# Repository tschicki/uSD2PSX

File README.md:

# About This Project

This variant of the [SD2PSX](https://github.com/sd2psx) is made specifically as an accessory for my [PlayStation 2](https://github.com/tschicki/PS2-Portable) portable.  
- Its electronics are based on and essentially 1:1 compatible to the original SD2PSX.  
- Form factor and pinout match an SD card, with one deviation: PS2 memory cards have an ACK signal that SD cards do not have - this is connected to pin 9, instead of DAT2.  
- While the *uSD2PSX* will fit in any SD card slot, only a PS2 will be able to access it.  
- The *uSD2PSX* may be used together with a regular PS2 console too, using a modified Bitfunx MX4SIO memory card.

# Parts Overview
This repo contains the design files (KiCad 7 & SolidWorks Maker) and the manufacturing files for the PCBs and 3D printed parts. Below are the required components to order/print.

## uSD2PSX Base PCB
- [KiCad project](https://github.com/tschicki/uSD2PSX/tree/main/uSD2PSX_Base)
- [Gerber files](https://github.com/tschicki/uSD2PSX/tree/main/uSD2PSX_Base/Gerber)
- [BOM](https://github.com/tschicki/uSD2PSX/tree/main/uSD2PSX_Base/bom)
- Supplier: JLCPCB
- Type: 2-Layer rigid
- Thickness: 0.6mm
- Copper: 1oz
- Plating: ENIG
- Via: tented or plugged

## uSD2PSX Contacts PCB
- [KiCad project](https://github.com/tschicki/uSD2PSX/tree/main/uSD2PSX_Contacts)
- [Gerber files](https://github.com/tschicki/uSD2PSX/tree/main/uSD2PSX_Contacts/Gerber)
- BOM: N/A
- Supplier: JLCPCB
- Type: 2-Layer rigid
- Thickness: 0.8mm
- Copper: 1oz
- Plating: ENIG
- Via: tented or plugged

## uSD2PSX Needle Probe
- [KiCad project](https://github.com/tschicki/uSD2PSX/tree/main/uSD2PSX_Adapter)
- [Gerber files](https://github.com/tschicki/uSD2PSX/tree/main/uSD2PSX_Adapter/Gerber)
- [BOM](https://github.com/tschicki/uSD2PSX/tree/main/uSD2PSX_Adapter/bom)
- Supplier: JLCPCB
- Type: 2-Layer rigid
- Thickness: 1.2mm
- Copper: 1oz
- Plating: HASL
- Via: tented or plugged

## uSD2PSX Cover
- [STEP & STL](https://github.com/tschicki/uSD2PSX/tree/main/uSD2PSX_3D/Export)
- 3D printed at 0.12mm layer height

## uSD2PSX Needle Probe Parts
- *Clip* and *Aligner*
- [STEP & STL](https://github.com/tschicki/uSD2PSX/tree/main/uSD2PSX_3D/Export)
- 3D printed

# Assembly uSD2PSX

## CBA Assembly
- First populate the *uSD2PSX Base* PCB according to its BOM, either manually or with stencil & paste. 
- Apply solder/paste on the pads intended for the *uSD2PSX Contacts* PCB and place it there. 
- Heat the assembly either with hot air or in a reflow oven and ensure that Base & Contacts are aligned without a gap between them.
- Check for shorts and clean the resulting assembly.

## SD Card Preparation
- Download the latest the SD2PSXtd firmware for SD2PSX. Find it [here](https://sd2psxtd.github.io).
- [PS2 Homebre Store](https://ps2homebrewstore.com/exploits/loadbooter-sd2psx/) has an awesome SD2PSX setup guide and pre-configured SD card image
- Prepare the SD card according to the instructions there

## Programming
- Plug the prepared micro SD card into the *uSD2PSX* assembly
- Place the assembly in the *uSD2PSX* Needle Probe and close it.
- Enter the RP2040 USB bootloader by plugging the *uSD2PSX Needle Probe* into a PC while holding the Bootsel button
- Drag the SD2PSXtd firmware image (.uf2) into the SD2PSX explorer window
- Unplug the *uSD2PSX Needle Probe*

## Setup
- Plug the *uSD2PSX Needle Probe* back into the PC
- The OLED should now display the SD2PSX menu, use the buttons SW1 and SW2 to navigate it
- Deploy CIV.bin in the menu
- Set Autoboot=ON and Mode=PS2 in the menu
- The *uSD2PSX* should now be configured, unplug it and preferrably give it a try on a PS2
- When you are sure that the *uSD2PSX* works as intended, adhere the *uSD2PSX Cover* using 2-3 small drops of glue. Ensure that no glue enters the micro SD card slot.
- As a last step, add a sticker on the top side to protect the testpoints, it should be betwen 0.1 and 0.2mm thickness

# Assembly uSD2PSX Needle Probe

- Populate the *uSD2PSX Needle Probe* CBA according to its BOM
- Clean the assembly
- Solder the 0.96 inch I2C OLED (same as SD2PSX) to the CBA
- Fix the printed Aligner to the CBA using 4 M1.6x5mm screws

# Modify a MX4SIO to work with uSD2PSX

The easiest and cleanest looking way to connect the *uSD2PSX* to a stock console is to modify a Bitfunx MX4SIO adapter.  
Buy a Bitfunx MX4SIO with SD card slot (beware, they also sell micro SD versions!) and open it up.
Remove R5 and solder a wire from it to the leftmost pin of the SD card slot. This will connect the ACK signal back to its original pin.

# Thanks!
Thanks to everyone working on SD2PSX and the awesome SD2PSXtd firmware!  
And thanks to everyone involved in [PS2 Homebre Store](https://ps2homebrewstore.com), it's awesome to see easily accessible apps and guides!

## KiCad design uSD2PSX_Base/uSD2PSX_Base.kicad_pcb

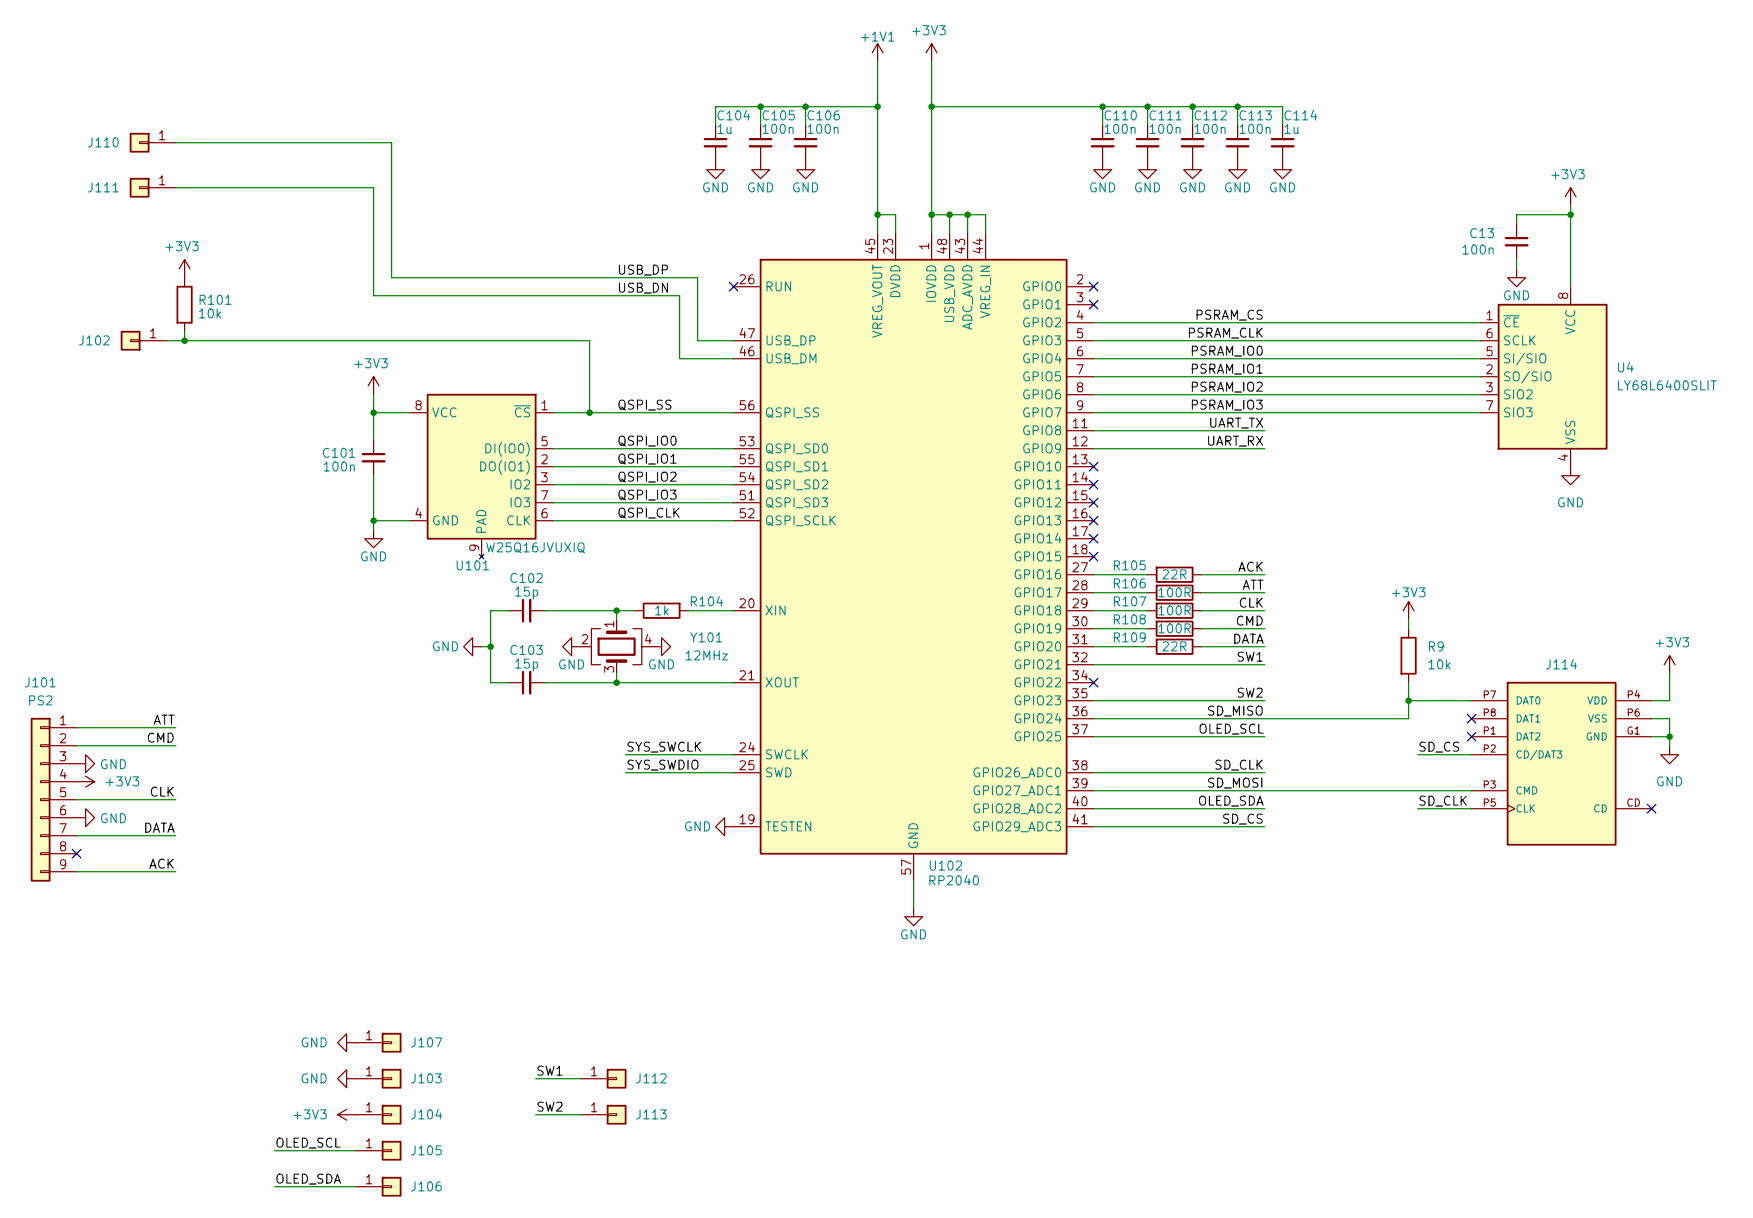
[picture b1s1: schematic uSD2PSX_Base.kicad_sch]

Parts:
C13, C101, C105, C106, C110, C111, C112, C113: 100n; C_0402_1005Metric; Part Number CC0402KRX7R7BB104
C102, C103: 15p; C_0402_1005Metric; Part Number CC0402JRNPO9BN150
C104, C114: 1u; C_0402_1005Metric; Part Number CC0603KRX7R7BB105
J101: PS2; uSD2PSX_Base
J102: BSEL; TestPoint_Pad_D1.5mm
J103, J107, J112: GND; TestPoint_Pad_D1.5mm
J104, J113: 3V3; TestPoint_Pad_D1.5mm
J105: SCL; TestPoint_Pad_D1.5mm
J106: SDA; TestPoint_Pad_D1.5mm
J110: DP; TestPoint_Pad_D1.5mm
J111: DN; TestPoint_Pad_D1.5mm
J114: MEM2085-00-115-00-A_REV0.2; GCT_MEM2085-00-115-00-A_REV0.2; Part Number MEM2085-00-115-00-A
R9, R101: 10k; R_0402_1005Metric; Part Number RC0402JR-0710KL
R104: 1k; R_0402_1005Metric; Part Number RC0402FR-071KL
R105, R109: 22R; R_0402_1005Metric; Part Number RC0402FR-0722RL
R106, R107, R108: 100R; R_0402_1005Metric; Part Number RC0402JR-07100RL
U4: LY68L6400SLIT; IC_W25Q16JVUXIQ_TR; Part Number APS6404L-3SQR-ZR; LCSC C261881
U101: W25Q16JVUXIQ; WSON-8-1EP_6x5mm_P1.27mm_EP3.4x4.3mm; Part Number W25Q16JVUXIQ TR
U102: RP2040; QFN-56-1EP_7x7mm_P0.4mm_EP3.2x3.2mm; Part Number RP2040
Y101: 12MHz; Crystal_SMD_3225-4Pin_3.2x2.5mm; Part Number FL1200112

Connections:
+1V1: C104.1, C105.1, C106.1, U102.23 (DVDD), U102.45 (VREG_VOUT), U102.50 (DVDD)
+3V3: C13.1, C101.1, C110.1, C111.1, C112.1, C113.1, C114.1, J101.4, J104.1, J114.P4 (VDD), R9.1, R101.1, U4.8 (VCC), U101.8 (VCC), U102.1 (IOVDD), U102.10 (IOVDD), U102.22 (IOVDD), U102.33 (IOVDD), U102.42 (IOVDD), U102.43 (ADC_AVDD), U102.44 (VREG_IN), U102.48 (USB_VDD), U102.49 (IOVDD)
/ACK: J101.9, R105.1
/ATT: J101.1, R106.1
/CLK: J101.5, R107.1
/CMD: J101.2, R108.1
/DATA: J101.7, R109.1
/OLED_SCL: J105.1, U102.37 (GPIO25)
/OLED_SDA: J106.1, U102.40 (GPIO28_ADC2)
/PSRAM_CLK: U4.6 (SCLK), U102.5 (GPIO3)
/PSRAM_CS: U4.1 (~CE), U102.4 (GPIO2)
/PSRAM_IO0: U4.5 (SI/SIO), U102.6 (GPIO4)
/PSRAM_IO1: U4.2 (SO/SIO), U102.7 (GPIO5)
/PSRAM_IO2: U4.3 (SIO2), U102.8 (GPIO6)
/PSRAM_IO3: U4.7 (SIO3), U102.9 (GPIO7)
/QSPI_CLK: U101.6 (CLK), U102.52 (QSPI_SCLK)
/QSPI_IO0: U101.5 (DI(IO0)), U102.53 (QSPI_SD0)
/QSPI_IO1: U101.2 (DO(IO1)), U102.55 (QSPI_SD1)
/QSPI_IO2: U101.3 (IO2), U102.54 (QSPI_SD2)
/QSPI_IO3: U101.7 (IO3), U102.51 (QSPI_SD3)
/QSPI_SS: J102.1, R101.2, U101.1 (~CS), U102.56 (QSPI_SS)
/SD_CLK: J114.P5 (CLK), U102.38 (GPIO26_ADC0)
/SD_CS: J114.P2 (CD/DAT3), U102.41 (GPIO29_ADC3)
/SD_MISO: J114.P7 (DAT0), R9.2, U102.36 (GPIO24)
/SD_MOSI: J114.P3 (CMD), U102.39 (GPIO27_ADC1)
/SW1: J112.1, U102.32 (GPIO21)
/SW2: J113.1, U102.35 (GPIO23)
/SYS_SWCLK: U102.24 (SWCLK)
/SYS_SWDIO: U102.25 (SWD)
/UART_RX: U102.12 (GPIO9)
/UART_TX: U102.11 (GPIO8)
/USB_DN: J111.1, U102.46 (USB_DM)
/USB_DP: J110.1, U102.47 (USB_DP)
GND: C13.2, C101.2, C102.1, C103.1, C104.2, C105.2, C106.2, C110.2, C111.2, C112.2, C113.2, C114.2, J101.3, J101.6, J103.1, J107.1, J114.G1 (GND), J114.G2 (GND__1), J114.G3 (GND__2), J114.G4 (GND__3), J114.G5 (GND__4), J114.G6 (GND__5), J114.G7 (GND__6), J114.G8 (GND__7), J114.G9 (GND__8), J114.G10 (GND__9), J114.P6 (VSS), U4.4 (VSS), U101.4 (GND), U102.19 (TESTEN), U102.57 (GND), Y101.2, Y101.4
unnamed: C102.2, R104.1, Y101.1
unnamed: R105.2, U102.27 (GPIO16)
unnamed: R106.2, U102.28 (GPIO17)
unnamed: R107.2, U102.29 (GPIO18)
unnamed: R108.2, U102.30 (GPIO19)
unnamed: R109.2, U102.31 (GPIO20)
unnamed: R104.2, U102.20 (XIN)
unnamed: C103.2, U102.21 (XOUT), Y101.3

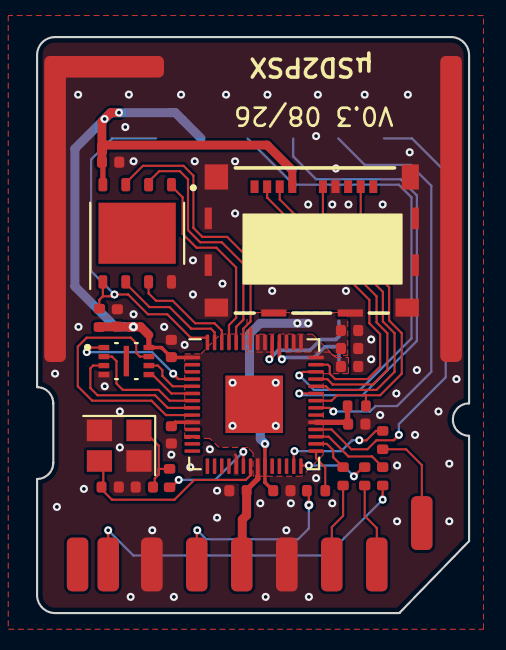
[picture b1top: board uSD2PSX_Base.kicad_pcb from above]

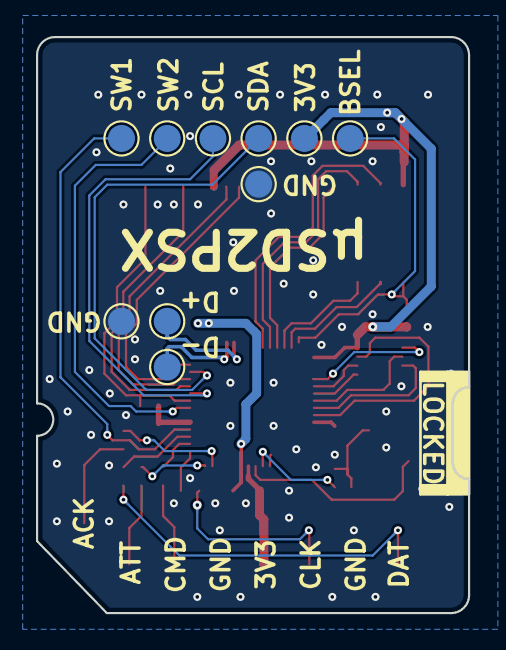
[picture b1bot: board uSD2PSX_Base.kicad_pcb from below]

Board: 2 copper layers, 24.0 x 32.0 mm, 36 parts (11 on the bottom side), 38 nets.

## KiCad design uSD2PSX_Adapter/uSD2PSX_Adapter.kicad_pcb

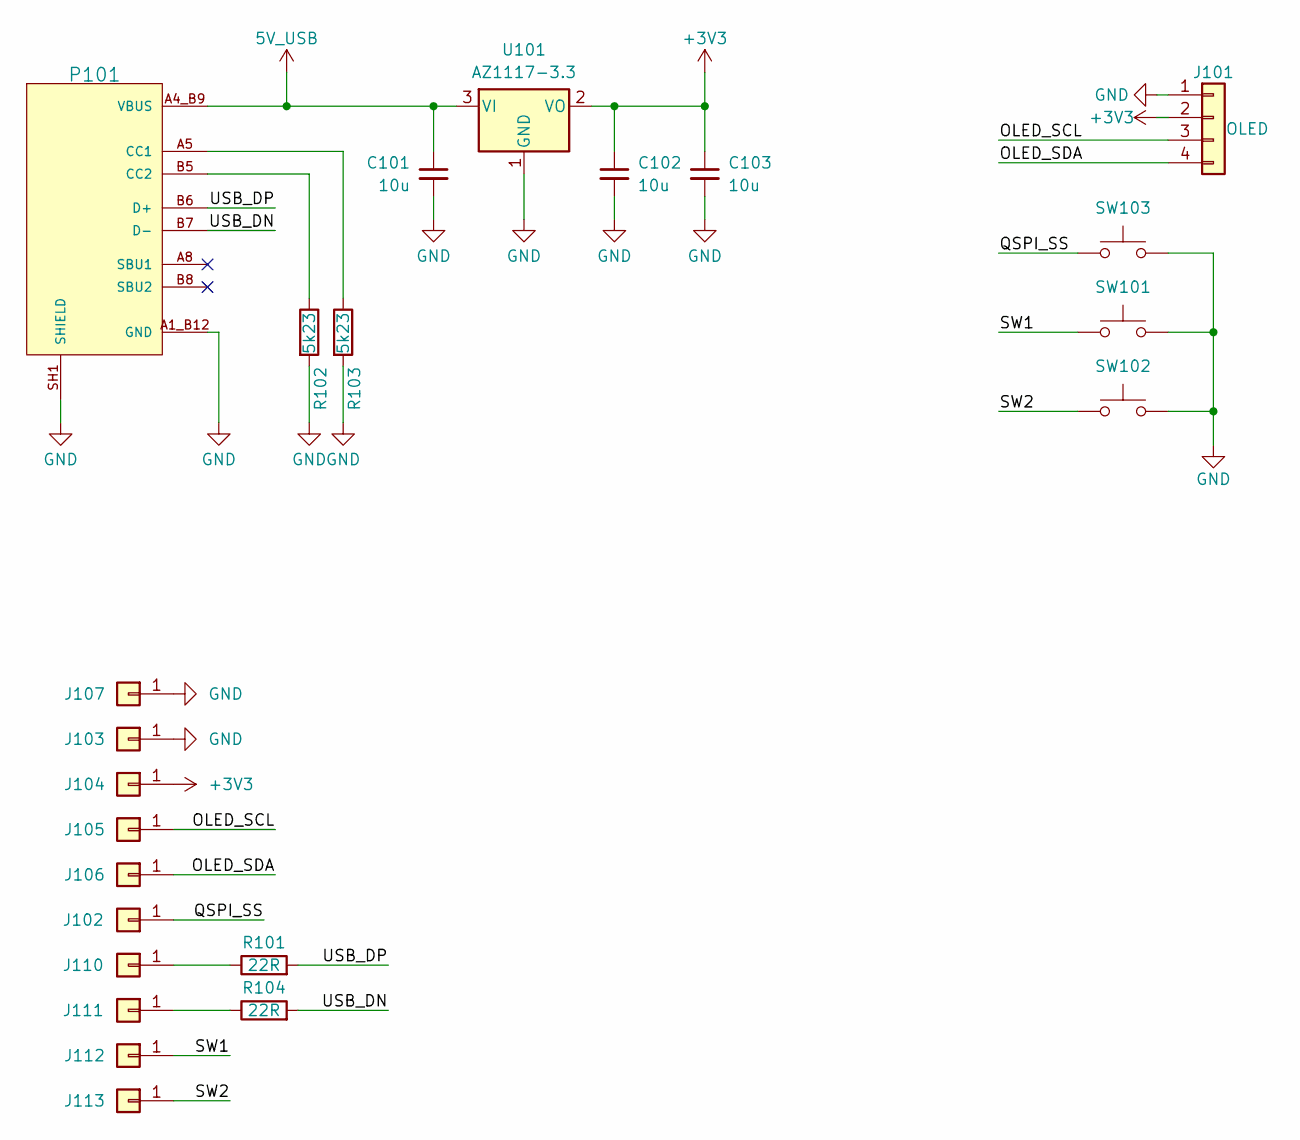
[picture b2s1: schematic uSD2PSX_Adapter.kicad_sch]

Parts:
C101, C102, C103: 10u; C_0805_2012Metric; Part Number TMK212BBJ106MGHT
J101: OLED; OLED_128x64
J102: BSEL; TestPoint_THTPad_D1.9mm_Drill0.6mm; Part Number 0906-0-15-20-76-14-11-0
J103, J107, J112: GND; TestPoint_THTPad_D1.9mm_Drill0.6mm; Part Number 0906-0-15-20-76-14-11-0
J104, J113: 3V3; TestPoint_THTPad_D1.9mm_Drill0.6mm; Part Number 0906-0-15-20-76-14-11-0
J105: SCL; TestPoint_THTPad_D1.9mm_Drill0.6mm; Part Number 0906-0-15-20-76-14-11-0
J106: SDA; TestPoint_THTPad_D1.9mm_Drill0.6mm; Part Number 0906-0-15-20-76-14-11-0
J110: DP; TestPoint_THTPad_D1.9mm_Drill0.6mm; Part Number 0906-0-15-20-76-14-11-0
J111: DN; TestPoint_THTPad_D1.9mm_Drill0.6mm; Part Number 0906-0-15-20-76-14-11-0
P101: 12402012E212A; AMPHENOL_12402012E212A; Part Number 12402012E212A
R101, R104: 22R; R_0402_1005Metric; Part Number RC0402FR-0722RL
R102, R103: 5k23; R_0402_1005Metric; Part Number RC0402FR-075K23L
SW101, SW102, SW103: SW_Push; SW_TL3301AF160QG; Part Number TL3301AF160QG
U101: AZ1117-3.3; SOT-223-3_TabPin2; Part Number AZ1117CH-3.3TRG1

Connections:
5V_USB: C101.1, P101.A4_B9 (VBUS), P101.B4_A9 (VBUS__1), U101.3 (VI)
+3V3: C102.1, C103.1, J101.2, J104.1, U101.2 (VO)
/OLED_SCL: J101.3, J105.1
/OLED_SDA: J101.4, J106.1
/QSPI_SS: J102.1, SW103.1
/SW1: J112.1, SW101.1
/SW2: J113.1, SW102.1
/USB_DN: P101.A7 (D-), P101.B7 (D-), R104.2
/USB_DP: P101.A6 (D+), P101.B6 (D+), R101.2
GND: C101.2, C102.2, C103.2, J101.1, J103.1, J107.1, P101.A1_B12 (GND), P101.B1_A12 (GND__1), P101.SH1 (SHIELD), P101.SH2 (SHIELD__1), P101.SH3 (SHIELD__2), P101.SH4 (SHIELD__3), R102.2, R103.2, SW101.2, SW102.2, SW103.2, U101.1 (GND)
unnamed: J110.1, R101.1
unnamed: J111.1, R104.1
unnamed: P101.A5 (CC1), R103.1
unnamed: P101.B5 (CC2), R102.1

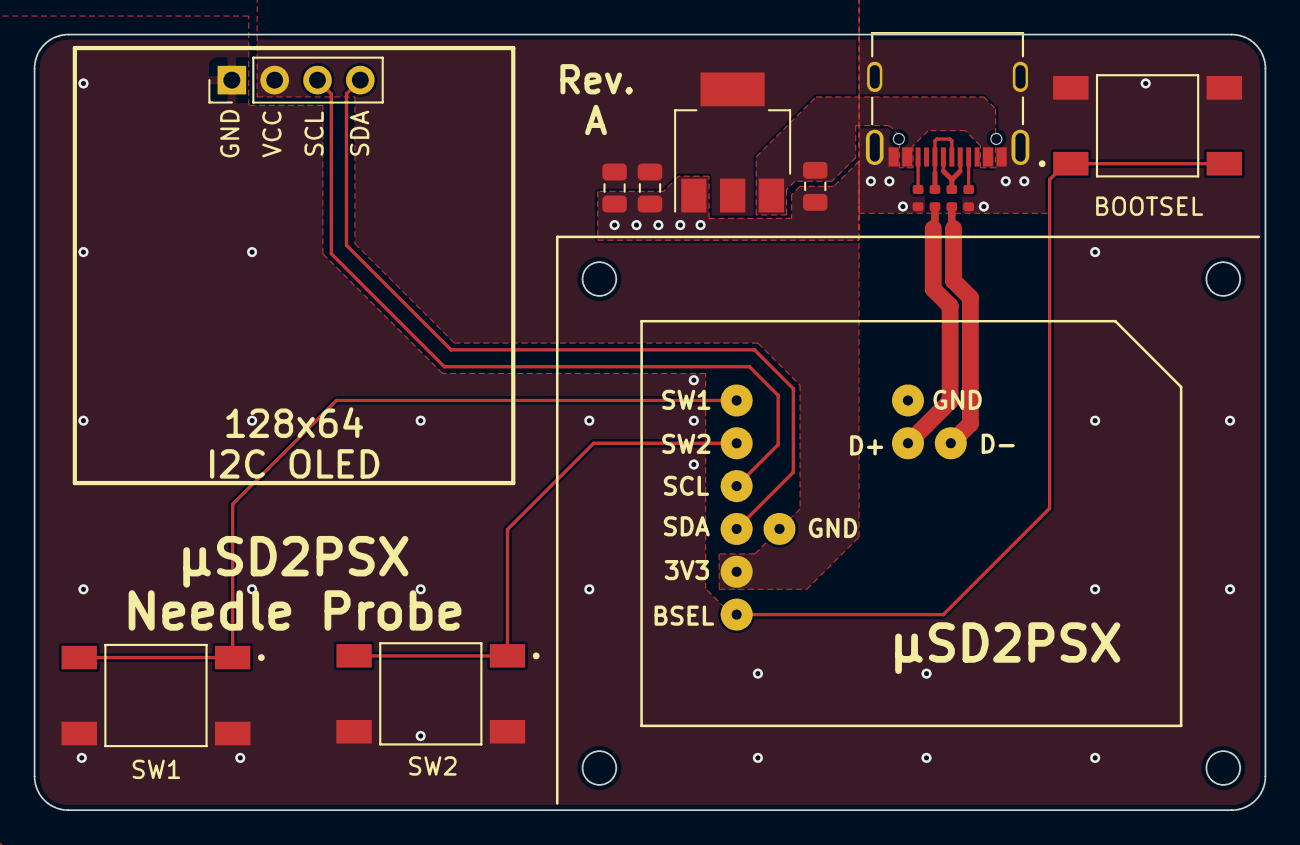
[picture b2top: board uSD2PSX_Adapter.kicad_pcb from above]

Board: 2 copper layers, 73.0 x 46.0 mm, 23 parts (0 on the bottom side), 14 nets.
